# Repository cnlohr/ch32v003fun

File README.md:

# ch32fun

An open source development environment (tooling, headers, examples) for the [CH32V003](http://www.wch-ic.com/products/CH32V003.html) (and many other chips within the CH32V family) with gcc-riscv64 that can be used in Windows (Native), Linux and/or WSL.  The CH32V003 is 10-cent part with a RISC-V EC core that runs at 48MHz, has 16kB of flash and 2kB of RAM and a bunch of peripherals.  It also comes in SOP-8, QFN-20 and SOIC packages.  You can get the datasheet [here](http://www.wch-ic.com/downloads/CH32V003DS0_PDF.html).

The goal of this project is to develop the tooling and environment for efficient use of the CH32V003.  Avoid complicated HALs, and unleash the hardware! The existing EVT is massive, and dev environment weighty.  This project specifically avoids the HAL and makes it so you can just use the [TRM](http://www.wch-ic.com/downloads/CH32V003RM_PDF.html). In contrast, blinky is only 500 bytes with ch32fun, boots faster, and significantly simpler overall.

ch32fun contains:
1. Examples using ch32fun, but not as many as using the HAL.  Most of which are centered around the ch32v003, but even many of those are compatible with other processors.
2. "minichlink" which uses the WCH CH-Link with libusb, for cross-platform use.
  * An STM32F042 Programmer, the [NHC-Link042](https://github.com/NgoHungCuong/NHC-Link042)
  * An ESP32S2 Programmer, the [esp32s2-funprog](https://github.com/cnlohr/esp32s2-cookbook/tree/master/ch32v003programmer)
  * The official WCH Link-E Programmer.
  * An Arduino-based interface, [Ardulink](https://gitlab.com/BlueSyncLine/arduino-ch32v003-swio).
  * Supports gdbserver-style-debugging for use with Visual Studio.
  * Supports printf-over-single-wire. (At about 400kBaud)
3. An extra copy of libgcc so you can use unusual risc-v build chains, located in the `misc/libgcc.a`.
4. A folder named "ch32fun" containing a single self-contained source file and header file for compling apps for the ch32v003.
5. On some systems ability to "printf" back through
6. A demo bootloader.

## Other family support

Currently, there is experimental support for the ch32v103, ch32v203, ch32v208, ch32v303, ch32v305 and ch32v307.  GDB is mostly tested on the 003, but works, to a limited degree on the other processors.

## Getting Started

For installation / setup instructions, see the [wiki page here](https://github.com/cnlohr/ch32fun/wiki/Installation)

## Features!

###  A fast "printf" debug over the programming interface.

And by fast I mean very fast. Typically around 36kBytes/sec.

```
./minichlink -T | pv > /dev/null
Found ESP32S2 Programmer
 536KiB 0:00:15 [36.7KiB/s] [        <=>                     ]
```

You can just try out the debugprintf project, or call SetupDebugPrintf(); and printf() away.

### Debugging support!

Via gdbserver built into minichlink!  It works with `gdb-multiarch` as well as in Visual Studio Code 

## Building and Flashing

```
cd examples/blink
make
```

text = code, data = constants and initialization values, bss = uninitialized values.  
dec is the sum of the 3 and reflects the number of bytes in flash that will get taken up by the program.

The generated .bin is used by minichlink and the .hex file is compatible with the official WCH flash tool.  

## VSCode +/- PlatformIO

Note: PlatformIO is generally used for CI on this repo. While PlatformIO can be used to code and debug a ch32fun project inside VSCode, you can also do it completely without PlatformIO: For that, see [template project](https://github.com/cnlohr/ch32fun/tree/master/examples/template/.vscode).

This project can be built, uploaded and debugged with VSCode and the PlatformIO extension. Simply clone and open this project in VSCode and have the PlatformIO extension installed. Use the [project environment switcher](https://docs.platformio.org/en/latest/integration/ide/vscode.html#project-tasks) to select a specific example, such as "blink".

To create a new PlatformIO firmware project based on ch32fun, simply use the [PlatformIO Home](https://docs.platformio.org/en/latest/home/index.html)'s "New Project" wizard and set "Framework" to "ch32v003fun". There are [various examples](https://github.com/Community-PIO-CH32V/platform-ch32v/tree/develop/examples/blinky-ch32v003fun).

The equivalent [PlatformIO Core CLI](https://docs.platformio.org/en/latest/integration/ide/vscode.html#platformio-core-cli) command would be
```sh
pio init -b genericCH32V003F4P6 -O "framework = ch32v003fun"
```

If you want to add your code directly to ch32fun project, please expand the available environments in the `platformio.ini` as [per instructions](https://github.com/cnlohr/ch32fun/blob/49640fbccf231191aa83c6a2bbe9d385535b2d1e/platformio.ini#L48-L53).

Please also note that when you open this project inside PlatformIO, you can use the [project environment switcher](https://docs.platformio.org/en/latest/integration/ide/vscode.html#project-tasks) at the bottom of the VSCode taskbar to select a specific example folder. Otherwise, "Build" will by default build **all** examples.

See [platform-ch32v](https://github.com/Community-PIO-CH32V/platform-ch32v) for further details and installation of the platform.

## clangd

If the C/C++ language server clangd is unable to find `ch32fun.h`, the example will have to be wiped `make clean` and built once with `bear -- make build`, which will generate a `compile_commands.json`, which clangd uses to find the include paths specified in the makefiles.  
`make clangd` does this in one step.
`build_all_clangd.sh` does in `build scripts` does this for all examples.

## Quick Reference
 * **REQUIRED** for programming/debugging: `SWIO` is on `PD1`. Do not re-use PD1 for multiple functions.
 * **OPTIONAL** `NRST` is on `PD7`. Not needed, defaults as GPIO in some configurations.
 * **OPTIONAL** UART `TX` is on: `PD5`. We recommend using SWIO for `printf` debugging.

## More examples / projects?

Other third party tools are adding lots of examples, etc.  See the following repos, for extra libraries, etc.
 * [ch32v003fun_wildwest](https://github.com/recallmenot/ch32v003fun_wildwest)
 * [ch32v003fun_libs](https://github.com/hexeguitar/ch32v003fun_libs)
 * [CH32V003_lib_uart](https://github.com/ADBeta/CH32V003_lib_uart)
 * [CH32Vxxx_lib_i2c](https://github.com/ADBeta/CH32Vxxx_lib_i2c)
 * [CH32Vxxx_lib_swi2c](https://github.com/ADBeta/CH32Vxxx_lib_swi2c)
 * [ch32v003fun_shenanigans](https://github.com/DeadBugEngineering/ch32v003fun_shenanigans)

## Support

You can open a github ticket or join my Discord in the #ch32fun channel.  Right now invites are private, so just ping me @cnlohr for an invite link.  My PMs are open.

### Footnotes/links

 * https://raw.githubusercontent.com/openwch/ch32v003/main/RISC-V%20QingKeV2%20Microprocessor%20Debug%20Manual.pdf Debugging Manual
 * http://www.wch-ic.com/downloads/QingKeV2_Processor_Manual_PDF.html Processor Manual
 * http://www.wch-ic.com/downloads/CH32V003RM_PDF.html Technical Reference Manual
 * http://www.wch-ic.com/downloads/CH32V003DS0_PDF.html Datasheet
 * https://github.com/CaiB/CH32V003-Architecture-Exploration/blob/main/InstructionTypes.md Details for the compressed ISA on this chip.
 * The CH32V003 has xv extensions, you can use this customized version of rvcodec.js to work with its opcodes: https://xw.macyler.moe/

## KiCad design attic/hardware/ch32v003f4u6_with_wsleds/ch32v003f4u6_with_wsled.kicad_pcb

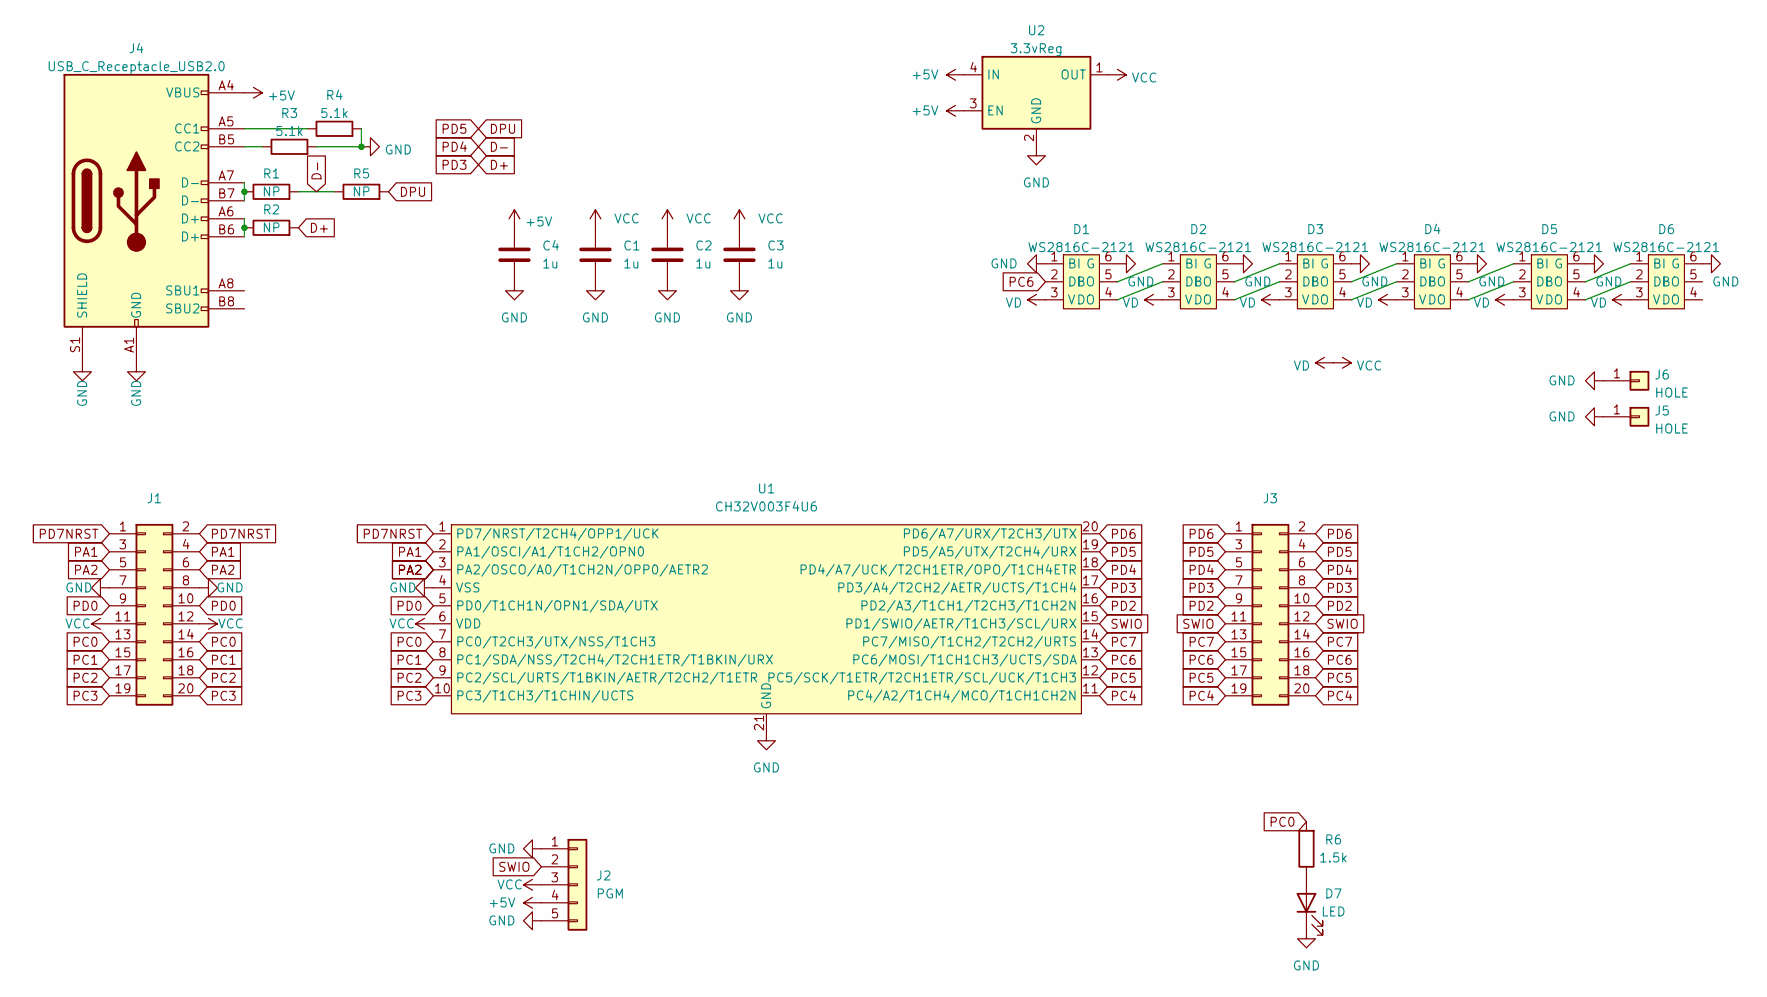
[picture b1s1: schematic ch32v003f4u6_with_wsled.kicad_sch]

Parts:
C1, C2, C3, C4: 1u; C_0402_1005Metric; LCSC C237173
D1, D2, D3, D4, D5, D6: WS2816C-2121; WS2816-2121; LCSC C965561
D7: LED; LED_0402_1005Metric; LCSC C74342
J1, J3: PinHeader_2x10_P2.54mm_Vertical; LCSC C124359
J2: PGM; PinHeader_1x05_P2.54mm_Vertical; LCSC C225257
J4: USB_C_Receptacle_USB2.0; USB_C_Receptacle_HRO_TYPE-C-31-M-12; LCSC C709358
J5, J6: HOLE; MountingHole_2.2mm_M2_DIN965_Pad
R1, R2, R5: NP; R_0402_1005Metric
R3, R4: 5.1k; R_0402_1005Metric; LCSC C258132
R6: 1.5k; R_0402_1005Metric; LCSC C25867
U1: CH32V003F4U6; QFN-20-1EP_3x3mm_P0.4mm_EP1.65x1.65mm; LCSC C5299908
U2: 3.3vReg; OnSemi_XDFN4-1EP_1.0x1.0mm_EP0.52x0.52mm; LCSC C81114

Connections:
+5V: C4.1, J2.4, J4.A4 (VBUS), J4.A9 (VBUS), J4.B4 (VBUS), J4.B9 (VBUS), U2.3 (EN), U2.4 (IN)
D+: J3.7, J3.8, R2.2, U1.17 (PD3/A4/T2CH2/AETR/UCTS/T1CH4)
D-: J3.5, J3.6, R1.2, R5.1, U1.18 (PD4/A7/UCK/T2CH1ETR/OPO/T1CH4ETR)
DPU: J3.3, J3.4, R5.2, U1.19 (PD5/A5/UTX/T2CH4/URX)
GND: C1.2, C2.2, C3.2, C4.2, D1.1 (BI), D1.6 (G), D2.6 (G), D3.6 (G), D4.6 (G), D5.6 (G), D6.6 (G), D7.1 (K), J1.7, J1.8, J2.1, J2.5, J4.A1 (GND), J4.A12 (GND), J4.B1 (GND), J4.B12 (GND), J4.S1 (SHIELD), J5.1, J6.1, R3.2, R4.2, U1.4 (VSS), U1.21 (GND), U2.2 (GND), U2.5 (GND)
unnamed: D1.4 (DO), D2.2 (DI)
unnamed: D1.5 (BO), D2.1 (BI)
unnamed: D2.4 (DO), D3.2 (DI)
unnamed: D2.5 (BO), D3.1 (BI)
unnamed: D3.4 (DO), D4.2 (DI)
unnamed: D3.5 (BO), D4.1 (BI)
unnamed: D4.4 (DO), D5.2 (DI)
unnamed: D4.5 (BO), D5.1 (BI)
unnamed: D5.4 (DO), D6.2 (DI)
unnamed: D5.5 (BO), D6.1 (BI)
unnamed: D7.2 (A), R6.1
unnamed: J4.A5 (CC1), R4.1
unnamed: J4.A6 (D+), J4.B6 (D+), R2.1
unnamed: J4.A7 (D-), J4.B7 (D-), R1.1
unnamed: J4.B5 (CC2), R3.1
PA1: J1.3, J1.4, U1.2 (PA1/OSCI/A1/T1CH2/OPN0)
PA2: J1.5, J1.6, U1.3 (PA2/OSCO/A0/T1CH2N/OPP0/AETR2)
PC0: J1.13, J1.14, R6.2, U1.7 (PC0/T2CH3/UTX/NSS/T1CH3)
PC1: J1.15, J1.16, U1.8 (PC1/SDA/NSS/T2CH4/T2CH1ETR/T1BKIN/URX)
PC2: J1.17, J1.18, U1.9 (PC2/SCL/URTS/T1BKIN/AETR/T2CH2/T1ETR)
PC3: J1.19, J1.20, U1.10 (PC3/T1CH3/T1CHIN/UCTS)
PC4: J3.19, J3.20, U1.11 (PC4/A2/T1CH4/MCO/T1CH1CH2N)
PC5: J3.17, J3.18, U1.12 (PC5/SCK/T1ETR/T2CH1ETR/SCL/UCK/T1CH3)
PC6: D1.2 (DI), J3.15, J3.16, U1.13 (PC6/MOSI/T1CH1CH3/UCTS/SDA)
PC7: J3.13, J3.14, U1.14 (PC7/MISO/T1CH2/T2CH2/URTS)
PD0: J1.9, J1.10, U1.5 (PD0/T1CH1N/OPN1/SDA/UTX)
PD2: J3.9, J3.10, U1.16 (PD2/A3/T1CH1/T2CH3/T1CH2N)
PD6: J3.1, J3.2, U1.20 (PD6/A7/URX/T2CH3/UTX)
PD7NRST: J1.1, J1.2, U1.1 (PD7/NRST/T2CH4/OPP1/UCK)
SWIO: J2.2, J3.11, J3.12, U1.15 (PD1/SWIO/AETR/T1CH3/SCL/URX)
VCC: C1.1, C2.1, C3.1, D1.3 (V), D2.3 (V), D3.3 (V), D4.3 (V), D5.3 (V), D6.3 (V), J1.11, J1.12, J2.3, U1.6 (VDD), U2.1 (OUT)

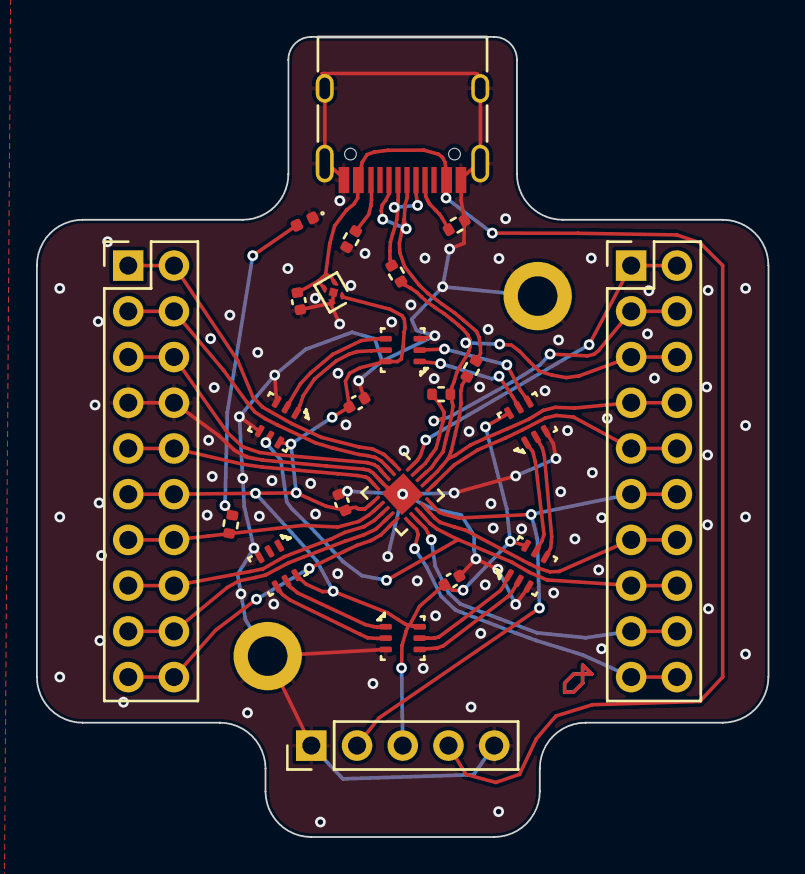
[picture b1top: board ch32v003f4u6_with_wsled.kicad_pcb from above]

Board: 2 copper layers, 40.6 x 44.5 mm, 25 parts (0 on the bottom side), 36 nets.

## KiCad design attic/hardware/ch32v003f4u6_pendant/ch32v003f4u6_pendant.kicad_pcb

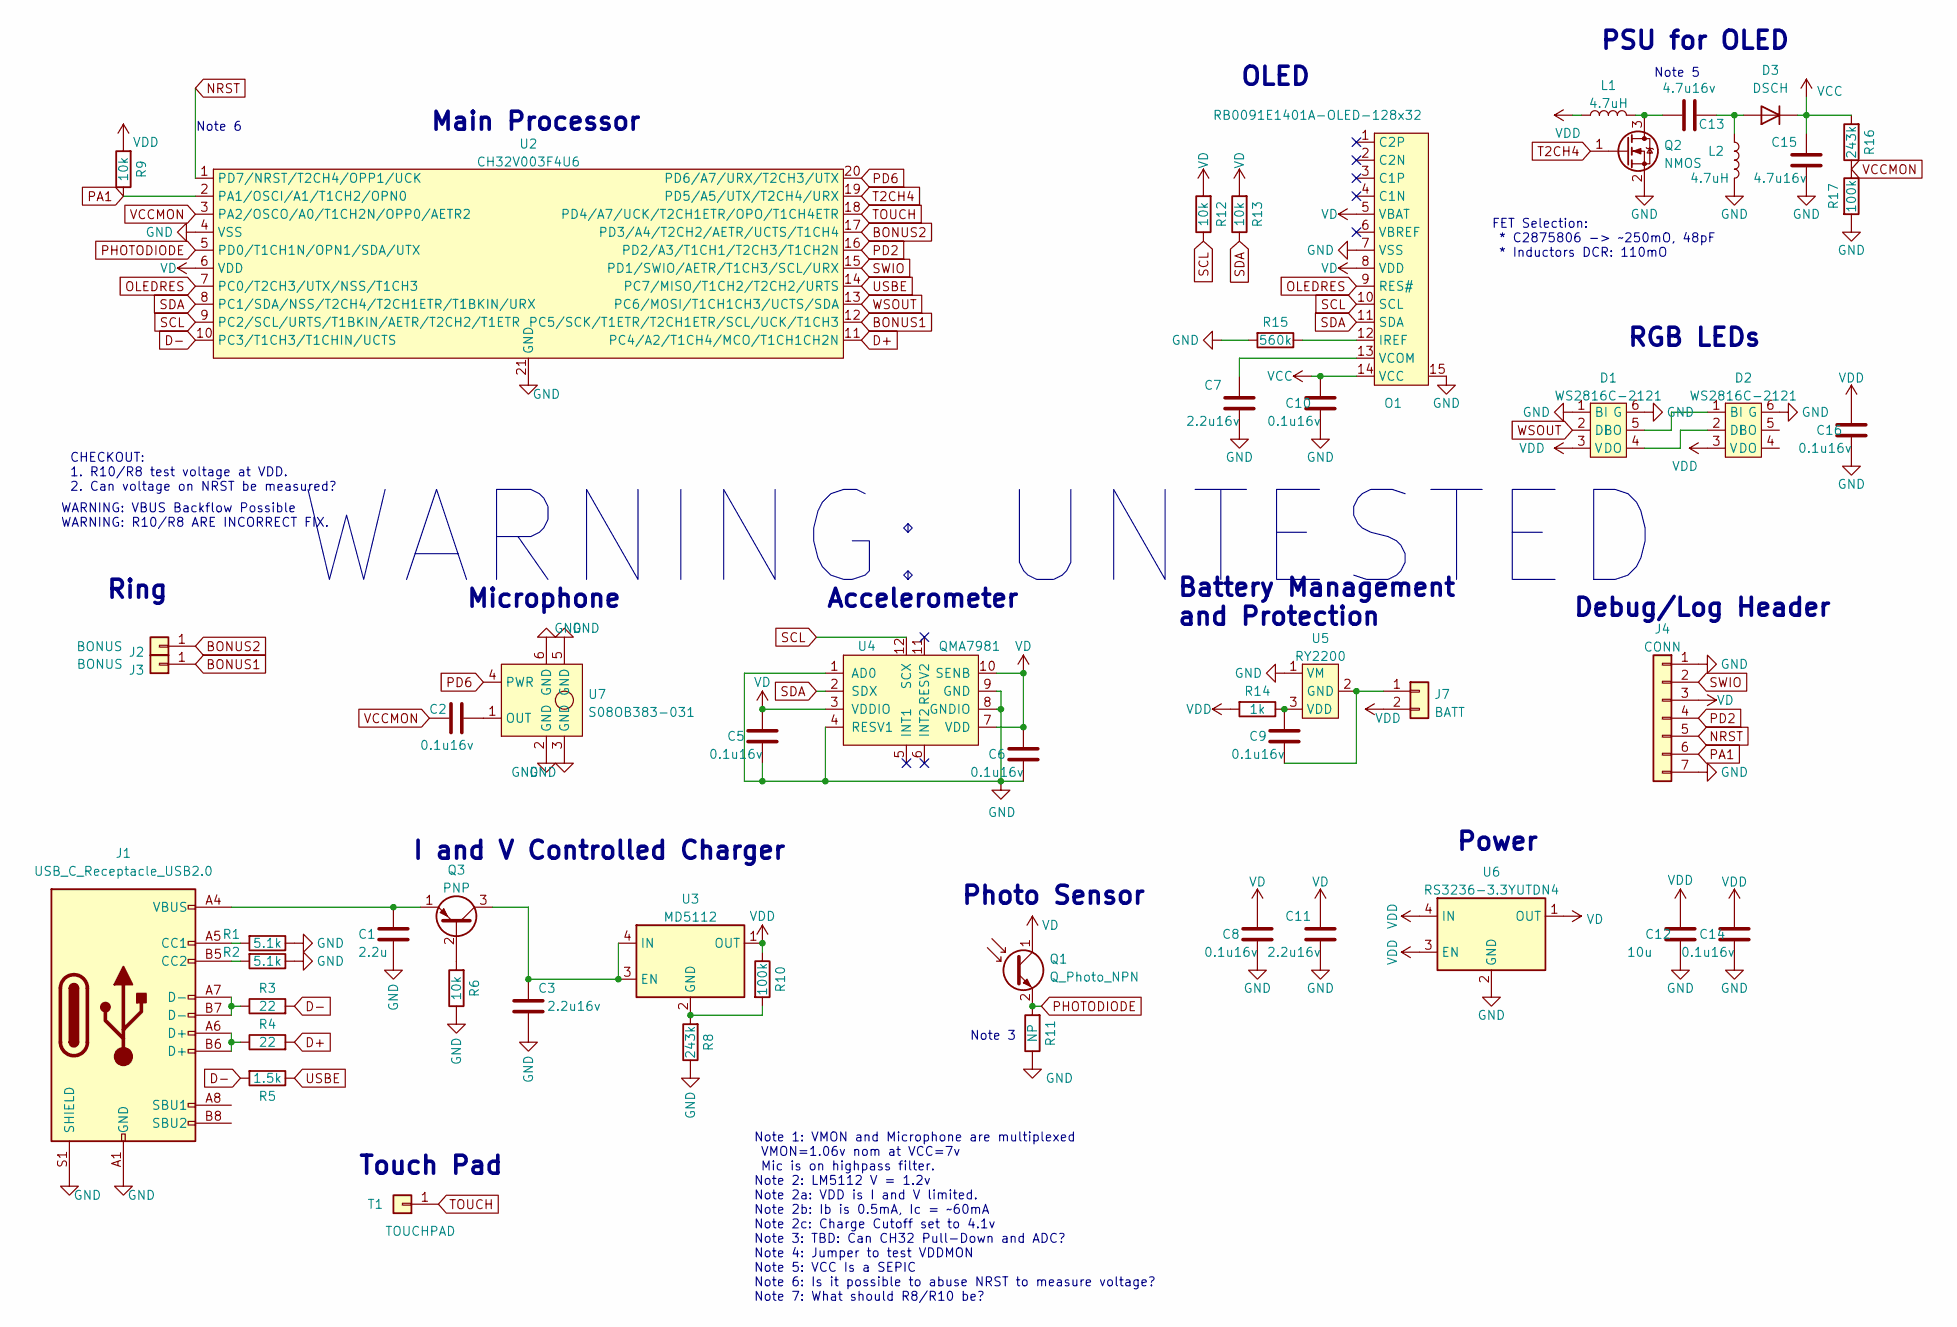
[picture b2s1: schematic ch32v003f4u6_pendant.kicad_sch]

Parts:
C1: 2.2u; C_0402_1005Metric; LCSC C385032
C2, C5, C6, C8, C9, C10, C14, C16: 0.1u16v; C_0402_1005Metric; LCSC C338032
C3, C7, C11: 2.2u16v; C_0402_1005Metric; LCSC C385032
C12: 10u; C_0402_1005Metric; LCSC C315248
C13, C15: 4.7u16v; C_0402_1005Metric; LCSC C412302
D1, D2: WS2816C-2121; WS2816-2121; LCSC C965561
D3: DSCH; D_SOD-323F; LCSC C255586
J1: USB_C_Receptacle_USB2.0; USB_C_Receptacle_HRO_TYPE-C-31-M-12; LCSC C2765186
J2, J3: BONUS; MountingHole_2.2mm_M2_DIN965_Pad
J4: CONN; PinHeader_1x07_P2.54mm_Vertical
J7: BATT; Hirose_DF13-02P-1.25DS_1x02_P1.25mm_Horizontal; LCSC C145979
L1, L2: 4.7uH; L_0805_2012Metric; LCSC C379996
O1: RB0091E1401A-OLED-128x32; RB0091E1401A-OLED-128x32_FLIP
Q1: Q_Photo_NPN; D_0805_2012Metric; LCSC C100090
Q2: NMOS; DFN-3L-1x0.6; LCSC C2875806
Q3: PNP; DFN-3L-1x0.6; LCSC C107421
R1, R2: 5.1k; R_0402_1005Metric; LCSC C114759
R3, R4: 22; R_0402_1005Metric; LCSC C102905
R5: 1.5k; R_0402_1005Metric; LCSC C114759
R6, R9, R12, R13: 10k; R_0402_1005Metric; LCSC C269674
R8, R16: 243k; R_0402_1005Metric; LCSC C43249
R10, R17: 100k; R_0402_1005Metric; LCSC C279979
R11: NP; R_0402_1005Metric
R14: 1k; R_0402_1005Metric; LCSC C279981
R15: 560k; R_0402_1005Metric; LCSC C137958
T1: TOUCHPAD; touchpad_10x6.5mm_retircle
U2: CH32V003F4U6; QFN-20-1EP_3x3mm_P0.4mm_EP1.65x1.65mm; LCSC C5299908
U3: MD5112; xdfn-reg; LCSC C919697
U4: QMA7981; QMA6981; LCSC C457290
U5: RY2200; SOT-23; LCSC C2888102
U6: RS3236-3.3YUTDN4; xdfn-reg; LCSC C379350
U7: S08OB383-031; GOERTEK-S08OB383-031-MemsMic; LCSC S08OB383-031

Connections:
BONUS1: J3.1, U2.12 (PC5/SCK/T1ETR/T2CH1ETR/SCL/UCK/T1CH3)
BONUS2: J2.1, U2.17 (PD3/A4/T2CH2/AETR/UCTS/T1CH4)
D+: R4.2, U2.11 (PC4/A2/T1CH4/MCO/T1CH1CH2N)
D-: R3.2, R5.2, U2.10 (PC3/T1CH3/T1CHIN/UCTS)
GND: C1.2, C3.2, C5.2, C6.2, C7.2, C8.2, C10.2, C11.2, C12.2, C14.2, C15.2, C16.2, D1.1 (BI), D1.6 (G), D2.6 (G), J1.A1 (GND), J1.A12 (GND), J1.B1 (GND), J1.B12 (GND), J1.S1 (SHIELD), J4.1, J4.7, L2.2, O1.7 (VSS), O1.15, Q2.2 (S), R1.1, R2.1, R6.1, R8.1, R11.1, R15.2, R17.2, U2.4 (VSS), U2.21 (GND), U4.1 (AD0), U4.4 (RESV1), U4.8 (GNDIO), U4.9 (GND), U5.1 (VM), U6.2 (GND), U6.5 (GND), U7.2 (GND), U7.3 (GND), U7.5 (GND), U7.6 (GND)
NRST: J4.5, U2.1 (PD7/NRST/T2CH4/OPP1/UCK)
unnamed: C1.1, J1.A4 (VBUS), J1.A9 (VBUS), J1.B4 (VBUS), J1.B9 (VBUS), Q3.1 (E)
unnamed: C2.2, U7.1 (OUT)
unnamed: C3.1, Q3.3 (C), U3.3 (EN), U3.4 (IN)
unnamed: C7.1, O1.13 (VCOM)
unnamed: C9.1, R14.1, U5.3 (VDD)
unnamed: C9.2, J7.1, U5.2 (GND)
unnamed: C13.1, L1.2, Q2.3 (D)
unnamed: C13.2, D3.2 (A), L2.1
unnamed: D1.4 (DO), D2.2 (DI)
unnamed: D1.5 (BO), D2.1 (BI)
unnamed: J1.A5 (CC1), R1.2
unnamed: J1.A6 (D+), J1.B6 (D+), R4.1
unnamed: J1.A7 (D-), J1.B7 (D-), R3.1
unnamed: J1.B5 (CC2), R2.2
unnamed: O1.12 (IREF), R15.1
unnamed: Q3.2 (B), R6.2
unnamed: R8.2, R10.2, U3.2 (GND), U3.5 (GND)
OLEDRES: O1.9 (RES#), U2.7 (PC0/T2CH3/UTX/NSS/T1CH3)
PA1: J4.6, R9.1, U2.2 (PA1/OSCI/A1/T1CH2/OPN0)
PD2: J4.4, U2.16 (PD2/A3/T1CH1/T2CH3/T1CH2N)
PD6: U2.20 (PD6/A7/URX/T2CH3/UTX), U7.4 (PWR)
PHOTODIODE: Q1.2 (E), R11.2, U2.5 (PD0/T1CH1N/OPN1/SDA/UTX)
SCL: O1.10 (SCL), R12.1, U2.9 (PC2/SCL/URTS/T1BKIN/AETR/T2CH2/T1ETR), U4.12 (SCX)
SDA: O1.11 (SDA), R13.1, U2.8 (PC1/SDA/NSS/T2CH4/T2CH1ETR/T1BKIN/URX), U4.2 (SDX)
SWIO: J4.2, U2.15 (PD1/SWIO/AETR/T1CH3/SCL/URX)
T2CH4: Q2.1 (G), U2.19 (PD5/A5/UTX/T2CH4/URX)
TOUCH: T1.1, U2.18 (PD4/A7/UCK/T2CH1ETR/OPO/T1CH4ETR)
USBE: R5.1, U2.14 (PC7/MISO/T1CH2/T2CH2/URTS)
VCC: C10.1, C15.1, D3.1 (K), O1.14 (VCC), R16.2
VCCMON: C2.1, R16.1, R17.1, U2.3 (PA2/OSCO/A0/T1CH2N/OPP0/AETR2)
VD: C5.1, C6.1, C8.1, C11.1, J4.3, O1.5 (VBAT), O1.8 (VDD), Q1.1 (C), R12.2, R13.2, U2.6 (VDD), U4.3 (VDDIO), U4.7 (VDD), U4.10 (SENB), U6.1 (OUT)
VDD: C12.1, C14.1, C16.1, D1.3 (V), D2.3 (V), J7.2, L1.1, R9.2, R10.1, R14.2, U3.1 (OUT), U6.3 (EN), U6.4 (IN)
WSOUT: D1.2 (DI), U2.13 (PC6/MOSI/T1CH1CH3/UCTS/SDA)

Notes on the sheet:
Accelerometer
Note 5
Ring
Microphone
Note 3
WARNING: UNTESTED
RGB LEDs
Battery Management and Protection
PSU for OLED
Debug/Log Header
OLED
FET Selection: * C2875806 -> ~250mO, 48pF * Inductors DCR: 110mO
Main Processor
Power
I and V Controlled Charger
Photo Sensor
Note 6
CHECKOUT: 1. R10/R8 test voltage at VDD. 2. Can voltage on NRST be measured?
Note 1: VMON and Microphone are multiplexed VMON=1.06v nom at VCC=7v Mic is on highpass filter. Note 2: LM5112 V = 1.2v Note 2a: VDD is I and V limited. Note 2b: Ib is 0.5mA, Ic = ~60mA Note 2c: Charge Cutoff set to 4.1v Note 3: TBD: Can CH32 Pull-Down and ADC? Note 4: Jumper to test VDDMON Note 5: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
WARNING: VBUS Backflow Possible WARNING: R10/R8 ARE INCORRECT FIX.
Touch Pad

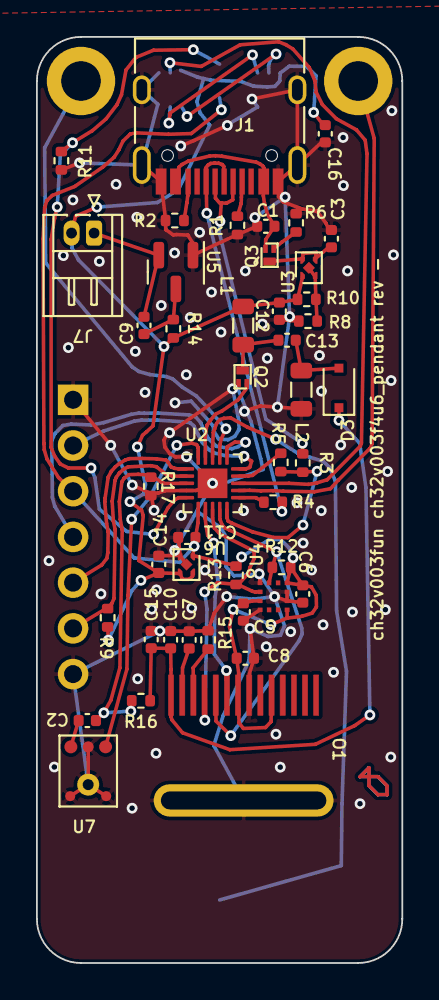
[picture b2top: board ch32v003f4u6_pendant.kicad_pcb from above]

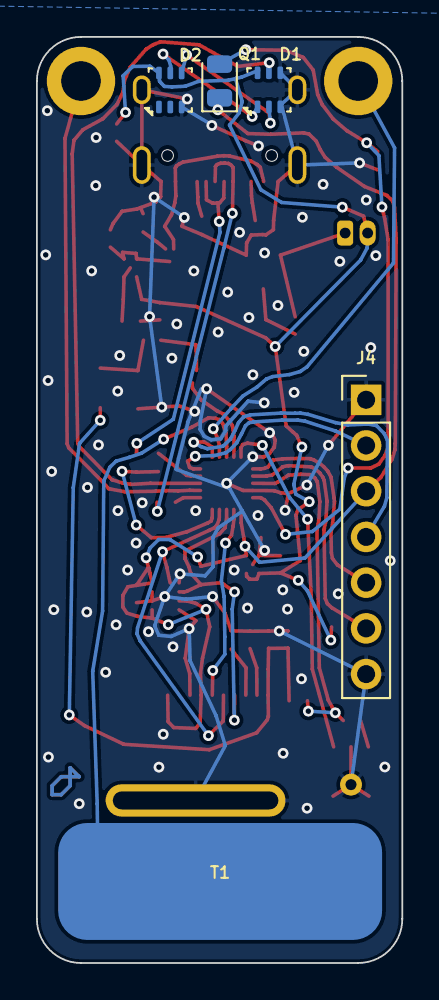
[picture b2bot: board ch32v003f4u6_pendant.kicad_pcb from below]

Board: 2 copper layers, 20.3 x 51.4 mm, 52 parts (5 on the bottom side), 39 nets.

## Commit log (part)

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2024-04-20 Progress but still no go
2024-04-20 Well, it enumerates.
2024-04-21 Tweak setupp ins
2024-04-21 Working device.
2024-04-21 Clean up some control flow.
2024-04-22 Things are working, but albeit with a bit of a cursed stint.
2024-04-22 Bump! Almost working hid reports.
2024-04-23 Cleanup forgot to commit last night
2024-04-23 Try to make CI happy
2024-04-23 Fix CI
2024-04-24 Add webusb demo
2024-04-24 Update with PD defines
2024-04-27 Fix 203 blink demo
2024-04-27 Add note about the attic
2024-04-27 Move some media
2024-04-27 Finish cleaning out the attic.
2024-05-01 Update README.md
    Corrects typo
2024-05-02 Update notes in DMA GPIO example
2024-06-10 Update ch32v003fun.c
    Declare the _write() function as "weak" to allow overriding for printf compatibility with external UART libraries (which support async R/W with DMA buffers and IRQ).
    See https://github.com/hexeguitar/ch32v003fun_libs/pull/3
2024-06-17 Make generated LD file rule .PHONY so that it always runs and avoids the possibility of an empty LD file from a previous failed run
2024-06-22 Add sh1107
2024-07-03 Relicense headers.
2024-07-04 1. Remove unused code. 2. Fix blink demo for x035 3. Fix x035 usage with Link-E v2.12
2024-07-04 Add CH32V203 USB (not yet working)
2024-07-05 Working on interrupt locations
2024-07-06 Remove plugdev warning on OSX
2024-07-07 we have enumeration
2024-07-07 Undo removal of Init from vector.
2024-07-07 Fix compile for USB project
2024-07-07 Fix remap code.
2024-07-07 Properly name descriptors
2024-07-08 Revert a few tweaks from before the 203 changes to simplify things, now that the issues have been ironed out.
2024-07-08 Oops fix naming
2024-07-08 Add gimbal picture
2024-07-08 Add note about way to close loop
2024-07-09 Switch to idiomatic IO output style.
2024-07-11 Fix == bug.
2024-07-12 Update LICENSE
2024-07-13 Various code cleanup + starting to address #344 and #343
2024-07-13 Allow only one instance of Delay_Tiny
2024-07-13 Fix asm -> __ASM
2024-07-13 Fix ld generation for CH32X035
2024-07-13 Relicense mini-printf under MIT license per mludvig approval.
2024-07-13 Add more notes about general usage.
2024-07-13 Fix back platform version
2024-07-14 Slight rewording of PlatformIO documentation
2024-07-14 Fixup README typos, slight addition
2024-07-15 Fix misleading GPIO MODE-names so that they represent the correct max frequency
2024-07-15 Make value of enum explicit
2024-07-15 Change instances of erroneous 50MHz in examples
2024-07-16 Add A. Mandera to LICENSE
2024-07-16 Remove init of unused pin
2024-07-17 Working on the 307's ethernet
2024-07-18 Added target for object file
2024-07-18 Move transfer initiation into a function
2024-07-18 Add a README
2024-07-18 Update README.md
    Added a mention of the initiate_transfer() function
2024-07-21 Trying to fix issue with enumerating
2024-07-24 Update c_cpp_properties.json
    Added missing slash in ch32v003fun path and added path to extralibs.
2024-07-30 Add TIM3 PWM example for CH32X035
2024-08-01 Fix support for Zephyr
2024-08-05 Move note about CPI/processor speeds in readmes (mostly to force github to know tip of master with CI)
2024-08-07 Add support for configuring flash / ram split
2024-08-09 Make blinke example rehomed ch32v003fun
2024-08-15 Drop unneeded zephyr module
2024-08-17 Weak linkage for symbols that might conflict with libc
2024-08-19 Add 305 printf demo
2024-08-22 Rebuild minichlink.exe on my pristine machine.
2024-08-27 Add some debugging
2024-08-30 Fix up x035 driver
2024-09-01 Autodetect ch32v003fun path.
2024-09-01 Migrate / unify usb_defines
2024-09-08 Added lib_rand library - provides rand() and seed() (32bit LFSR)
2024-09-09 fixed typos & made lfsr variable static
2024-09-13 fixed malformed target
2024-09-17 add setjmp/longjmp support
2024-09-18 Add more needed things to make the ethernet work.
2024-09-21 setjmp: add float support and more efficient jmp_buf
2024-09-24 Add test for GPIO
2024-09-25 Improved comments, added millis() macro, made example main() more useful
2024-09-25 Fixed typos
2024-09-25 Fix situation where the processor completly seizes up and can't be talked to silently crashing. These situations require user intervention.
2024-09-25 Fixup based on comments.
2024-09-27 Update demo + rename to make it clearer what it is.
2024-10-01 Update ch32v003fun.h
    Fix protection of zicsr-extension code.
2024-10-03 Split linker script
2024-10-07 Add bufen from reference manual as an optional other name for ADC output buffer enable/disable
2024-10-09 Fix typo
2024-10-09 Fix PIO build CI
2024-10-10 Fix detection of projects to build
    Restricts search of folders with `Makefile` file in them to only 2 folders deep as seen from the root, so `examples/blink/Makefile` is fine but ont `examples/blink/nested_util/Makefile`
2024-10-12 Add missing field from ethernet definitions.
2024-10-12 Add gigabit test example
2024-10-12 Fix table formatting
2024-10-14 Add chip info register defs
2024-10-14 Add RAM tester example
2024-10-14 Created an example for CH32V208WBU6 to check if it builds.
2024-10-14 Changes according to EVT
2024-10-16 Add bootloader option bytes
2024-10-21 Fix InterruptVectorDefault() for CH32V10x, CH32V20x and CH32V30x
2024-10-21 Fix interrupt handlers errors
2024-10-21 Fix error for ch32v10x
2024-10-25 Fixed indentation
2024-10-26 Fixed USB HS/FS in InterruptVectorDefault()
2024-10-26 Removed excess USB interrupt handlers defs
2024-10-28 [PIO] Fix include path for assembly files
    Needed for e.g. rv003usb.S that expects that it can find funconfig.h. This repo does not yet have any example that uses assembly files that need an include from an example folder, this is prophylacti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
2024-10-29 add timeout to WaitForDebuggerToAttach
2024-10-29 examples: update WaitForDebuggerToAttach() calls
2024-10-31 Use friendly defines for pin names
2024-10-31 Update gpio_and_adc.c
    just some small tweaks to help us newbs
2024-11-01 Add warning for future generations about how to flash the chip.
2024-11-06 Cleanup (macro algebra) the 30x interrupts.
2024-11-06 Whitespace
2024-11-07 Update hidapi-libusb (and let's see if CI is OK) Updated: * Linux * LibUSB * Windows * OSX
2024-11-11 Add the ability to use a ch32v003-based programmer
2024-11-11 Fix compile, and tweak wait for debugger work.
2024-11-11 Change behavior to: 1. Printf will wait up to 120ms at boot. 2. If printf has timed out, it will immediately continue. 3. If a debugger is reattached, it will keep printing. 4. If a debugger is attac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
2024-11-13 Add `make gdbclient` as a target.
2024-11-14 Add `make gdbclient` as a target and change single step behavior.
2024-11-15 * Optimize pgm-esp32-s2-ch32xx.c * Improve VS Code build * Fix stepping for older GDBs
2024-11-16 Fix compile, and tweak wait for debugger work.
    Change behavior to:
    1. Printf will wait up to 120ms at boot.
    2. If printf has timed out, it will immediately continue.
    3. If a debugger is reattached, it will keep printing.
    4. If a debugger is attached, it will wait up to 120ms. Then continue at full speed.
    Fix GDB on minichlink.
2024-11-16 Super unbrick mode now unlocked. It just continuously tries to unbrick.
2024-11-16 Working on trying to make the v307 unbrick work
2024-11-16 Fix unaligned (start address) writes.
2024-11-17 remove threads as a feature
2024-11-18 Add example for timer capture.
2024-11-20 Add HPE support
2024-11-21 Fixed endif
2024-11-22 Mirror c and s... let's try making s;c just single step normally.
2024-11-23 Fix debug break behavior.
2024-11-24 Fixed halt/resume on WCH-LinkE
2024-11-25 Update build and mechanism for minichlink
2024-11-26 Fix unitialized WCH-LinkE errors
2024-11-28 Add example for driving DMA WS2812B's on any port.
2024-12-02 Cleanup code based on montemonte's suggestions, and remove two extra sleep's which now can go about 4x faster on Windows
2024-12-02 ch32v003fun.h: Add missing partial-remap define for TIM1.
2024-12-02 examples: Add tim1_pwm_complementary_outputs example
    This example shows the use of complementary TIM1 outputs and
    how to change the deadtime setting.
2024-12-02 Remove unnecessary .gdbinit
2024-12-03 Update mini vs code projects to use 3333
2024-12-04 deprecate macos12
2024-12-05 Make the linker make the map file instead of it being a separate step becuase it tells you which libraries are actually being linked that way.
2024-12-10 Fix CH32V208 Zero Wait Flash and RAM size
2024-12-17 minichlink: add ch641
2024-12-25 this changes the standard mode of the CH32x035 to machine mode
2025-01-01 Fix __get_MEPC() so that, like other CSR get/set helper functions it enables Zicsr extension for GCC > 10
2025-01-08 Add interrupt test, for testing performance of EXTI interrupts in different scenarios
2025-01-08 Add overclocking test
2025-01-10 Allow OLED Custom sizes
2025-01-14 Include some documentation on how to conveniently install the udev rules.
2025-01-14 Duplicate all the udev rules for dialout
2025-01-18 CH32V003: Add accessors for DBGMCU_CR CSR register.
    Also correct bit definitions for that register.
2025-01-20 Add example of using DMA for phase-shifted PWM outputs.
2025-01-23 Active polling of Ardulink device
2025-01-29 Update transition helper
2025-02-03 * Convert ch32v003fun -> ch32fun * Split apart header into specific hardware devices.
2025-02-03 Fix compile for minichlink
2025-02-03 Fix CI linker script
2025-02-03 Fix OSX build
2025-02-03 Fix location of header copyright
2025-02-05 Add prototypes for printf functions + Add test Makefile for custom tests.
2025-02-06 Add a {} guard to get rid of gcc warning when compile for ch32v208
2025-02-06 Update exti_pin_change_isr.c
    Fix typo
2025-02-09 * Shrink the hardfault handler from about 1.5kB to about 180 bytes. * Fix async poll_input
2025-02-09 Fix compile/warning
2025-02-09 Cleanup inline assembly definitions.
2025-02-09 Fix ch32v30x PLL multiplication. Closes #498
2025-02-09 Move struct to protected location outside assembly compilation.
2025-02-09 Fix assembly guarding. Forgot to update blink.bin.
2025-02-09 Add basic 00x support + fix corner case input_poll situation
2025-02-09 Fix naming bug in DMA CFGR header for channel 4 to 7
2025-02-10 * Fix bad latency setting * Fix bad logic for printf with negative numbers.
2025-02-10 Add the CH32V00x series / #define to the build system
2025-02-10 Add zmmul to 006 (it seems to work!)
2025-02-10 put the extension in the wrong place
2025-02-12 Update ch32v003hw.h to the latest version
    Additionally, remove CH32V30x_D8C related macro
2025-02-12 Update ch32v10xhw.h to the latest version
    Update all peripheral headers except USB.
2025-02-13 Getting closer to a working example.
2025-02-13 Fix double clear
2025-02-13 Add const for some of the buffers
2025-02-13 Further increase clock rate to OLED
2025-02-13 Further optimize by using native bit width in more places.
2025-02-14 Update windows .exe from recent changes.
2025-02-14 Update windows minichlink exe
2025-02-17 Use constants/defines for FLASH_KEYx instead of magic numbers in flashtest example
2025-02-18 Unify EXTEN_BASE definition
    Both definitions of EXTEN_BASE are equivalent.
2025-02-19 Rename all AFIO_EXTICR_ defines to AFIO_EXTICR1_ for consistency
2025-02-23 Move the gp register, to allow the compiler to leverage gp to access the first part of ram. This produces smaller executables in general. I don't know why the original startup code pointed at 0x20000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
